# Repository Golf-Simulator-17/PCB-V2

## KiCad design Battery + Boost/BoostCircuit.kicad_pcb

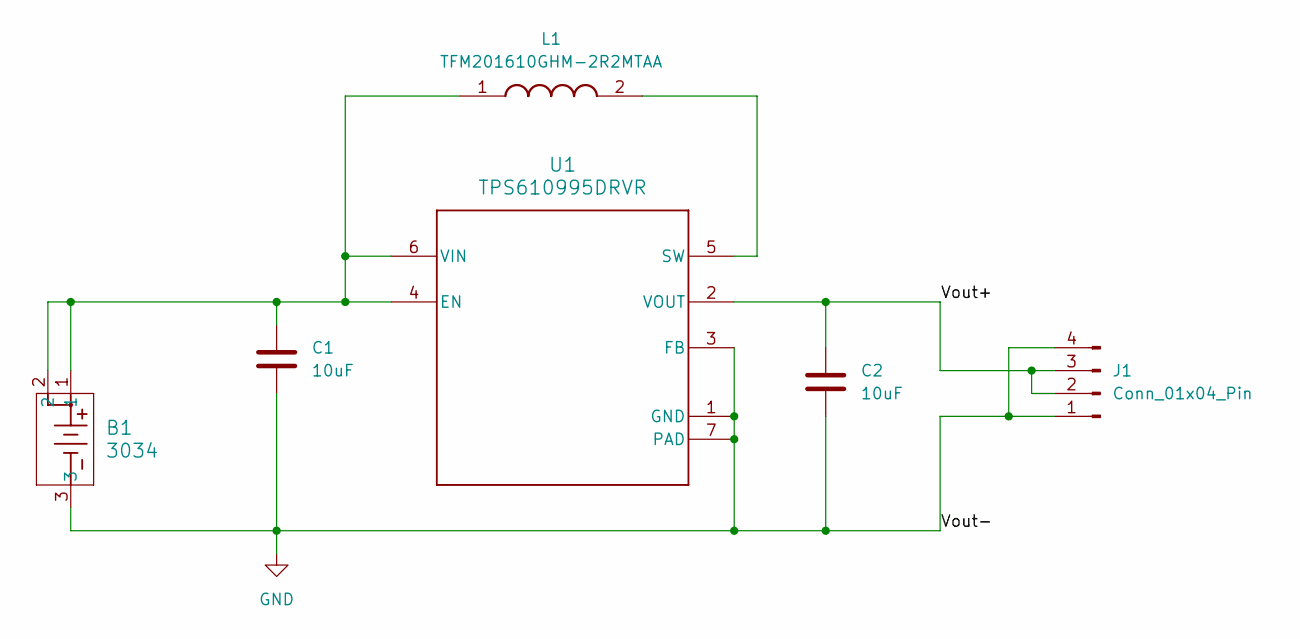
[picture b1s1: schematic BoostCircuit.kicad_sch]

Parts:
B1: 3034; 3034_KEY
C1: 10uF; C_0805_2012Metric
C2: 10uF; C_1206_3216Metric
J1: Conn_01x04_Pin; PinHeader_1x04_P2.54mm_Vertical
L1: TFM201610GHM-2R2MTAA; INDC2016X100N; Mouser Part Number 810-TFM201610GHM2R2A
U1: TPS610995DRVR; DRV0006A

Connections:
/Vout+: C2.1, J1.2, J1.3, U1.2 (VOUT)
GND: B1.3, C1.2, C2.2, J1.1, J1.4, U1.1 (GND), U1.3 (FB), U1.7 (PAD), U1.V
unnamed: B1.1, B1.2, C1.1, L1.1, U1.4 (EN), U1.6 (VIN)
unnamed: L1.2, U1.5 (SW)

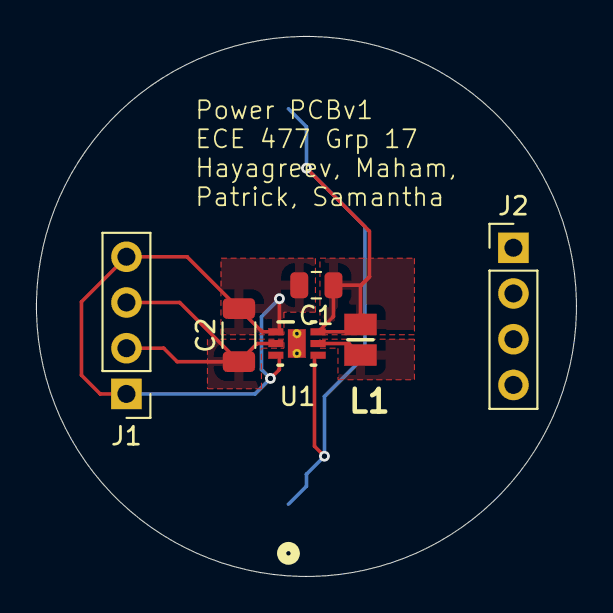
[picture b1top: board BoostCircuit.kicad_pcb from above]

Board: 2 copper layers, 30.0 x 30.0 mm, 7 parts (1 on the bottom side), 4 nets.

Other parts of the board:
J2: Conn_01x04_Pin; PinHeader_1x04_P2.54mm_Vertical

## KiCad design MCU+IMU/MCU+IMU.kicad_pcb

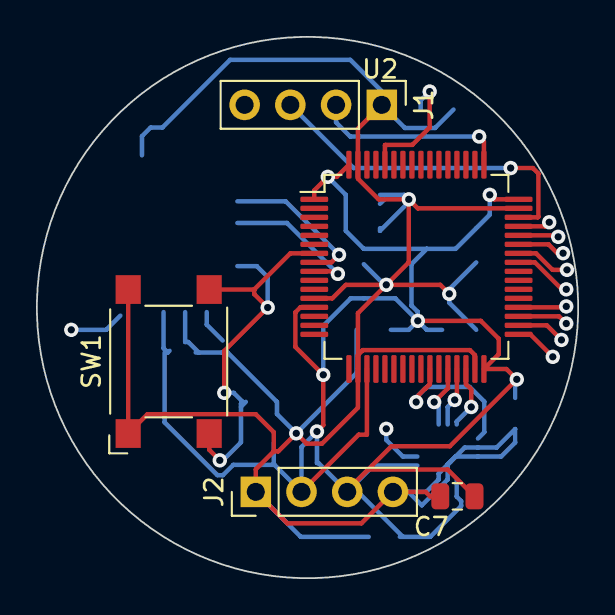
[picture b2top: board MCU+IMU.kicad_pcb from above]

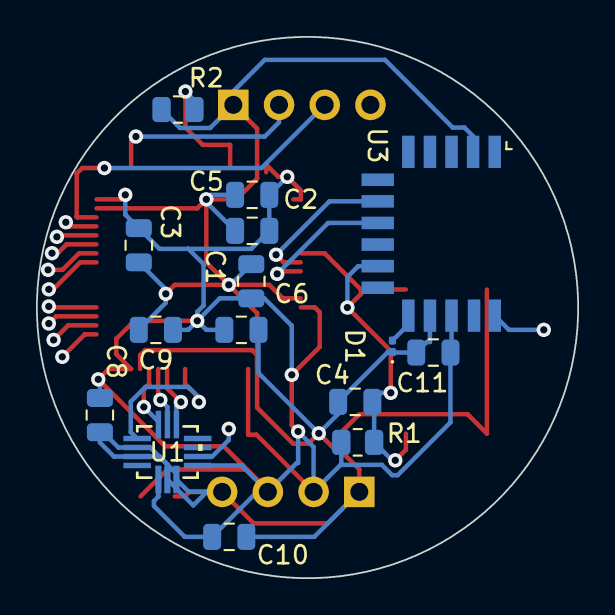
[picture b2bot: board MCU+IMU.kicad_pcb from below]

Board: 2 copper layers, 30.1 x 30.1 mm, 20 parts (15 on the bottom side), 13 nets.

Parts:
C1, C10, C11: 10u; C_0805_2012Metric
C2, C3, C4, C5, C6, C7, C8: 100n; C_0805_2012Metric
C9: 100nF; C_0805_2012Metric
D1: LED; LED_0201_0603Metric
J1: Conn_01x04_Male; PinHeader_1x04_P2.54mm_Vertical
J2: Conn_01x04; PinHeader_1x04_P2.54mm_Vertical
R1, R2: 100K; R_0805_2012Metric
SW1: SW_Push; SW_SPST_Omron_B3FS-100xP
U1: LSM6DSV16XTR; LGA14L_LSM6_STM
U2: STM32F091RCT6; LQFP-64_10x10mm_P0.5mm
U3: RN4871; Microchip_RN4871

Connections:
/BOOT0: R2.1, U2.60 (PF11)
/I2C2_SCL: U1.13 (SCL), U2.29 (PB10)
/I2C2_SDA: U1.14 (SDA), U2.30 (PB11)
/I2C_SA0: U1.1 (SDO/SA0), U2.26 (PB0)
/IMU Comm En: U1.12 (CS), U2.28 (PB2)
/NRST: C4.1, R1.2, SW1.2, U2.7 (NRST), U3.10 (RST)
/SWCLK: J1.3, U2.46 (PA13)
/SWDIO: J1.2, U2.49 (PA14)
/USART1_RX: U2.9 (PC1), U3.8 (UART_TX)
/USART1_TX: U2.8 (PC0), U3.7 (UART_RX)
GND: C1.2, C2.2, C3.2, C4.2, C5.2, C6.2, C7.2, C8.2, C9.2, C10.2, C11.2, D1.1 (K), J1.1, J2.1, J2.4, R2.2, SW1.1, U1.2 (SDx/AH1/QVAR1), U1.3 (SCx/AH2/QVAR2), U1.6 (GND), U1.7 (GND), U2.12 (VSSA), U2.18 (VSS), U2.31 (VSS), U2.47 (VSS), U2.63 (VSS), U3.2 (GND), U3.13 (GND)
unnamed: D1.2 (A), U3.12 (P0_2)
VDD: C1.1, C2.1, C3.1, C5.1, C6.1, C7.1, C8.1, C9.1, C10.1, C11.1, J2.2, J2.3, R1.1, U1.5 (VDD_IO), U1.8 (VDD), U2.1 (VBAT), U2.13 (VDDA), U2.19 (VDD), U2.32 (VDD), U2.48 (VDDIO2), U2.64 (VDD), U3.14 (VBAT)

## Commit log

2023-09-13 trial
2023-09-18 test
2023-09-20 new stuff
2023-09-27 PCB update
2023-09-27 change
2023-10-11 PCB Review 1
2023-10-23 Ordered
2023-11-28 final
